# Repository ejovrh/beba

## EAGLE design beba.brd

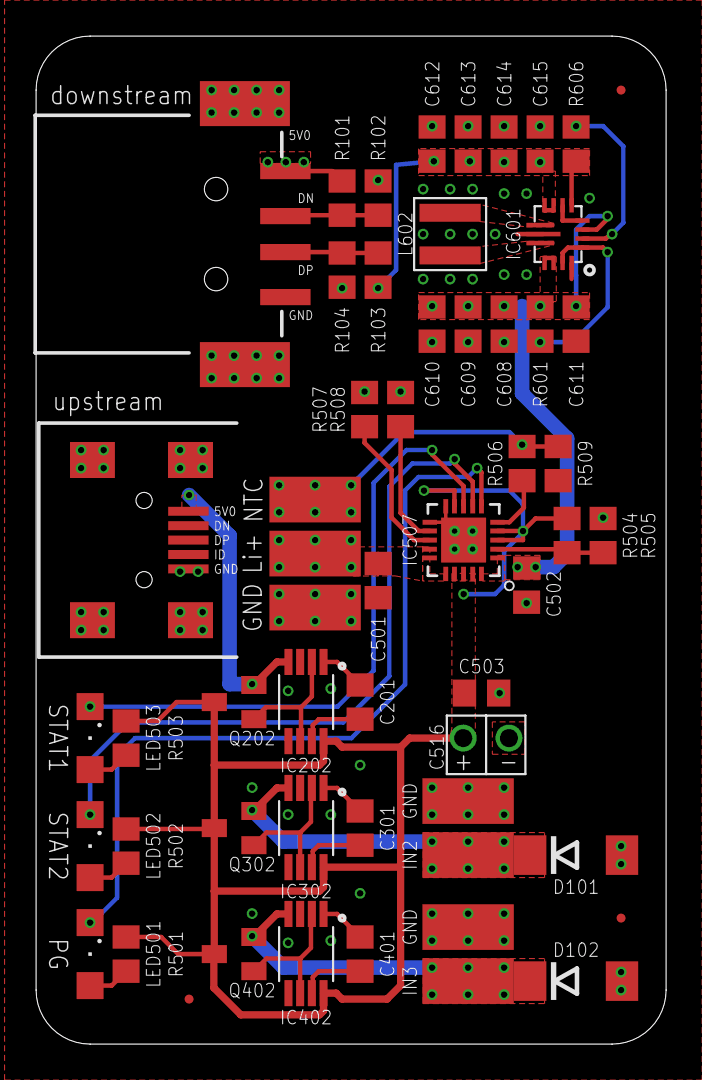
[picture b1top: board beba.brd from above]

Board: 2 copper layers, 35.0 x 56.0 mm, 56 parts (0 on the bottom side), 35 nets.

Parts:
C201, C301, C401: 0.1uF / 25V; C0805
C501, C502, C503, C608, C609, C610, C612: 10uF / 25V; C0805
C516: 6800uF / 16V; TH
C611: 0.1uF / 50V; C0805
C613, C614, C615: 22u / 25V; C0805
D101, D102: 3SMBJ5921B-TP; DO214AA
FID1, FID2, FID3: fiducial; FIDUCIAL_0.5MM
IC202, IC302, IC402: LM74670QDGKTQ1; VSSOP-8
IC507: 579-MCP73871T2CCIML; QFN50P400X400X100-21N
IC601: TPS630701RNMT; VQFN
L602: XFL4020-152MEC; 1616
LED501: LTST-C230KGKT - green; SML1206
LED502: LTST-C230KRKT - red; SML1206
LED503: LTST-C230KSKT - yellow; SML1206
PAD101: IN2; SMD2,54-5,08
PAD102, PAD104, PAD107: GND; SMD2,54-5,08
PAD103: IN3; SMD2,54-5,08
PAD105: NTC; SMD2,54-5,08
PAD106: Li-Ion +; SMD2,54-5,08
Q202, Q302, Q402: SQ2310ES-T1_BE3; SOT23
R101, R103: 75k; R0805
R102, R104: 49k9; R0805
R501, R502, R503, R506, R507: 1k; R0805
R504: 50k; R0805
R505, R508, R606: 100k; R0805
R509: 150k; R0805
R601: 10k; R0805
USB101: MUSBR-05-F-O-B-SM-A; SAMTEC_MUSBR-05-F-O-B-SM-A
USB102: USB-A-S-S-B-SM2; SAMTEC_USB-A-S-X-X-SM2

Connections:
5V0: C612.2, C613.2, C614.2, C615.2, IC601.5-FB, IC601.7-VOUT, IC601.8-VOUT, IC601.VOUT, R101.2, R103.2, R606.2, USB102.1_5V0
GND: C501.2, C502.2, C503.2, C516.NEG, C608.1, C609.1, C610.1, C611.1, C612.1, C613.1, C614.1, C615.1, D101.A, D102.A, IC507.10_GND1, IC507.11_GND2, IC507.GND2, IC507.GND3, IC507.GND4, IC507.GND5, IC507.GND6, IC601.4-GND, IC601.6-FB2, IC601.10-PGND, IC601.15-VSEL, PAD102.1, PAD104.1, PAD107.1, R102.1, R104.1, R505.1, R507.2, R508.2, R509.2, USB101.5_GND, USB101.G1, USB101.G2, USB101.G3, USB101.G4, USB102.4_GND, USB102.G1, USB102.G2
IDEAL_DIODE1:GATE_DRIVER: IC202.GATE_DRIVE, IC202.GATE_PULLD, Q202.1
IDEAL_DIODE1:VCAPH: C201.2, IC202.VCAPH
IDEAL_DIODE1:VCAPL: C201.1, IC202.VCAPL
IDEAL_DIODE2:GATE_DRIVER: IC302.GATE_DRIVE, IC302.GATE_PULLD, Q302.1
IDEAL_DIODE2:VCAPH: C301.2, IC302.VCAPH
IDEAL_DIODE2:VCAPL: C301.1, IC302.VCAPL
IDEAL_DIODE3:GATE_DRIVER: IC402.GATE_DRIVE, IC402.GATE_PULLD, Q402.1
IDEAL_DIODE3:VCAPH: C401.2, IC402.VCAPH
IDEAL_DIODE3:VCAPL: C401.1, IC402.VCAPL
MCP73871-1:LED1_A: LED501.A, R501.2
MCP73871-1:LED2_A: LED502.A, R502.2
MCP73871-1:LED3_A: LED503.A, R503.2
MCP73871-1:PG: IC507.!6_PG!, LED501.C
MCP73871-1:PROG1: IC507.13_PROG1, R507.1
MCP73871-1:PROG3: IC507.12_PROG3, R508.1
MCP73871-1:STAT1: IC507.8_STAT1/!LBO!, LED503.C
MCP73871-1:STAT2: IC507.7_STAT2, LED502.C
MCP73871-1:THERM: IC507.5_THERM, R506.1
MCP73871-1:VPCC: IC507.2_VPCC, R504.1, R505.2
NTC: PAD105.1, R506.2, R509.1
TPS630701-1:L1: IC601.11-L1, L602.P$1
TPS630701-1:L2: IC601.9-L2, L602.P$2
TPS630701-1:N$8: IC601.1-PS/S, IC601.14-EN, R601.1
TPS630701-1:PG1: IC601.2-PG, R606.1
TPS630701-1:VAUX: C611.2, IC601.3-VAUX
USBDN: R101.1, R102.2, USB102.2_DN
USBDP: R103.1, R104.2, USB102.3_DP
VINPUT1: IC202.ANODE, Q202.2, USB101.1_VCC
VINPUT2: D101.C, IC302.ANODE, PAD101.1, Q302.2
VINPUT3: D102.C, IC402.ANODE, PAD103.1, Q402.2
V_INPUT: C503.1, C516.POS, IC202.CATHODE, IC302.CATHODE, IC402.CATHODE, IC507.3_SEL, IC507.4_PROG2, IC507.9_!TE!, IC507.17_CE, IC507.18_IN1, IC507.19_IN2, Q202.3, Q302.3, Q402.3, R501.1, R502.1, R503.1, R504.2
V_LIION+: C501.1, IC507.14_VBAT1, IC507.15_VBAT2, IC507.16_BAT_SENSE, PAD106.1
V_REGULATED: C502.1, C608.2, C609.2, C610.2, IC507.1_OUT1, IC507.20_OUT2, IC601.12-VIN, IC601.13-VIN, IC601.VIN, R601.2

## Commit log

2017-05-09 - quick and dirty schematic and layout of a powerbank device
2017-05-09 - added usb socket and datasheets
2017-05-28 - added DE1205-18 Power Inductor library
2017-05-28 - corrected issues with component placement, power inductor footprint, etc.
2017-05-28 - added MX500075-1517 USB Mini-B straight socket datasheet
2017-05-28 - further minor corrections
2017-08-20 - minor corrections, added bom
2017-12-24 - added eagle.epf
2019-01-02 - recreated epf - eagle project identifier file
2022-04-24 - rewrote schematic into sheets
2022-04-27 - finalized rev.1 schematic, ERC checks out OK - compiled BOM
2022-04-28 - moved over voltage protection diode to forward of ideal diode and duplicated it for the other non-USB input channel - updated BOM
2022-04-28 - minor updates to components
2022-04-28 - added fiducials
2022-04-28 - uploaded brd to fab - created gerber files - rev.1 finished
2022-05-28 - changed positions of red and green led
2022-05-29 - optimization of BOM: replaced MCP73871's VPCC 50k resistor with 49.9k
2022-05-29 - exchanged passives (capacitors with higher voltage, resistors with higher power rating), updated BOM
2022-05-29 locked PCB edge, USB connector and LED positions
2022-05-29 case development: added eagle export (dxf) and newly created dwg
2022-05-30 start of rev.2 board - increased uninterrupted copper below MCP73871 for better cooling - removed bottom copper contacts for IN1/IN2, GND and similar - replaced MCP73871's big input cap from TH to SM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
2022-05-30 further work on rev.2 board: - increased copper below MCP73871 even more - replaced solder pads for LiIon battery with SMD JST-PH connector
2022-06-02 more work
2022-06-02 - MCP73871's input capacitor: moved square bottom pour from positive (falsely placed) to negative (correct placement), added same square to top layer
